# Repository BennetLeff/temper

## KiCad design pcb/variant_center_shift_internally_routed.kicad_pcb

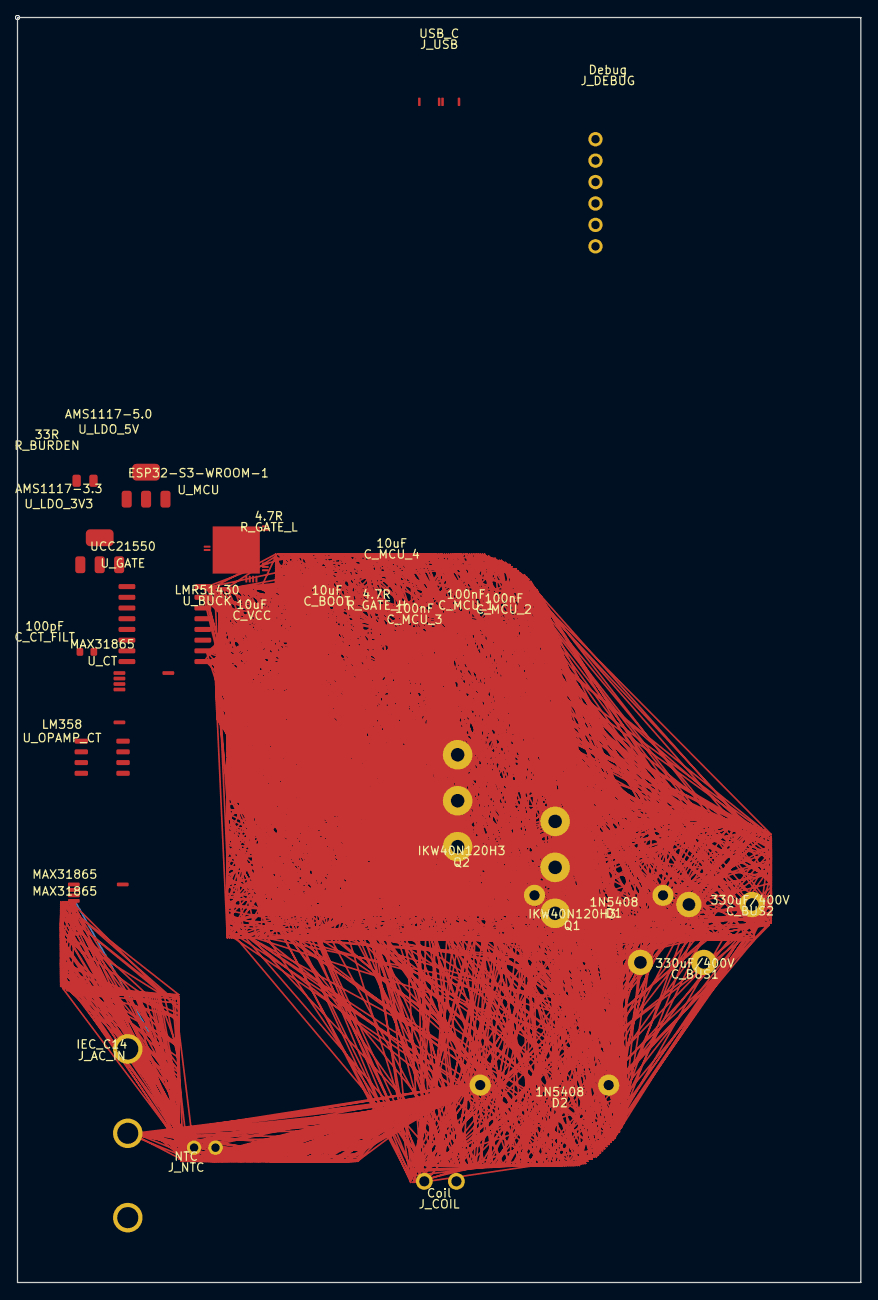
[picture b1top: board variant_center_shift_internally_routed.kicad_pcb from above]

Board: 4 copper layers, 100.0 x 150.0 mm, 33 parts (0 on the bottom side), 23 nets.

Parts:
C_BOOT: 10uF; C_0805_2012Metric
C_BUS1, C_BUS2: 330uF/400V; CP_Radial_D18.0mm_P7.50mm
C_CT_FILT: 100pF; C_0603_1608Metric
C_MCU_1, C_MCU_2, C_MCU_3: 100nF; C_0402_1005Metric
C_MCU_4: 10uF; C_0402_1005Metric
C_VCC: 10uF; C_0805_2012Metric
D1, D2: 1N5408; D_DO-201AD_P15.24mm_Horizontal
J_AC_IN: IEC_C14; IEC_C14_Male
J_COIL: Coil; PhoenixContact_MCV_1,5_2-G-3.81_1x02_P3.81mm_Vertical
J_DEBUG: Debug; PinHeader_1x06_P2.54mm_Vertical
J_NTC: NTC; PinHeader_1x02_P2.54mm_Vertical
J_USB: USB_C; USB_C_Receptacle_HRO_TYPE-C-31-M-12
MAX31865: MAX31865; TSSOP-20_4.4x6.5mm_P0.65mm
MH1, MH2, MH3, MH4: MountingHole_3.2mm_M3
Q1, Q2: IKW40N120H3; TO-247-3_Horizontal_TabDown
R_BURDEN: 33R; R_0805_2012Metric
R_GATE_H: 4.7R; R_0805_2012Metric
R_GATE_L: 4.7R; R_0805_2012Metric
U_BUCK: LMR51430; SOT-23-6
U_CT: MAX31865; TSSOP-20_4.4x6.5mm_P0.65mm
U_GATE: UCC21550; SOIC-16W_7.5x10.3mm_P1.27mm
U_LDO_3V3: AMS1117-3.3; SOT-223-3_TabPin2
U_LDO_5V: AMS1117-5.0; SOT-223-3_TabPin2
U_MCU: ESP32-S3-WROOM-1; QFN-56-1EP_7x7mm_P0.4mm_EP5.6x5.6mm
U_OPAMP_CT: LM358; SOIC-8_3.9x4.9mm_P1.27mm

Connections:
+3V3: C_MCU_1.1, C_MCU_2.1, C_MCU_3.1, C_MCU_4.1, J_DEBUG.2, MAX31865.20, U_CT.20, U_LDO_3V3.2, U_LDO_3V3.4, U_MCU.1
+5V: U_BUCK.2, U_BUCK.4, U_LDO_3V3.3, U_LDO_5V.2, U_LDO_5V.4, U_OPAMP_CT.7, U_OPAMP_CT.8
+15V: C_VCC.1, U_BUCK.3, U_GATE.1, U_GATE.11, U_LDO_5V.3
AC_L: D1.1, J_AC_IN.1
AC_N: D2.2, J_AC_IN.2
CGND: C_VCC.2, U_GATE.5, U_GATE.6, U_GATE.7, U_GATE.8
DC_BUS+: C_BUS1.1, C_BUS2.1, D1.2, Q1.3
GATE_H: Q1.1, R_GATE_H.1, R_GATE_H.2, U_GATE.15
GATE_L: Q2.1, R_GATE_L.1, R_GATE_L.2, U_GATE.10
GND: C_CT_FILT.2, C_MCU_1.2, C_MCU_2.2, C_MCU_3.2, C_MCU_4.2, J_AC_IN.3, J_COIL.2, J_DEBUG.1, J_NTC.2, J_USB.A1, J_USB.A12, MAX31865.10, R_BURDEN.2, U_BUCK.1, U_BUCK.5, U_BUCK.6, U_CT.10, U_LDO_3V3.1, U_LDO_5V.1, U_MCU.2, U_MCU.57, U_OPAMP_CT.4
I_SENSE: C_CT_FILT.1, R_BURDEN.1, U_MCU.15, U_OPAMP_CT.1, U_OPAMP_CT.2, U_OPAMP_CT.3, U_OPAMP_CT.5, U_OPAMP_CT.6
PGND: C_BUS1.2, C_BUS2.2, Q2.2, U_GATE.12, U_GATE.13
PWM_H: U_GATE.2, U_MCU.13
PWM_L: U_GATE.3, U_MCU.14
SPI_CLK: MAX31865.1, U_CT.1, U_MCU.20
SPI_CS_TEMP: U_CT.4, U_MCU.23
SPI_MISO: MAX31865.3, U_CT.3, U_MCU.22
SPI_MOSI: MAX31865.2, U_CT.2, U_MCU.21
SW_NODE: C_BOOT.2, J_COIL.1, Q1.2, Q2.3, U_GATE.9, U_GATE.16
TEMP_SENSE: J_NTC.1, MAX31865.4
USB_D+: J_USB.A6, U_MCU.40
USB_D-: J_USB.B6, U_MCU.41
VCC_BOOT: C_BOOT.1, U_GATE.14

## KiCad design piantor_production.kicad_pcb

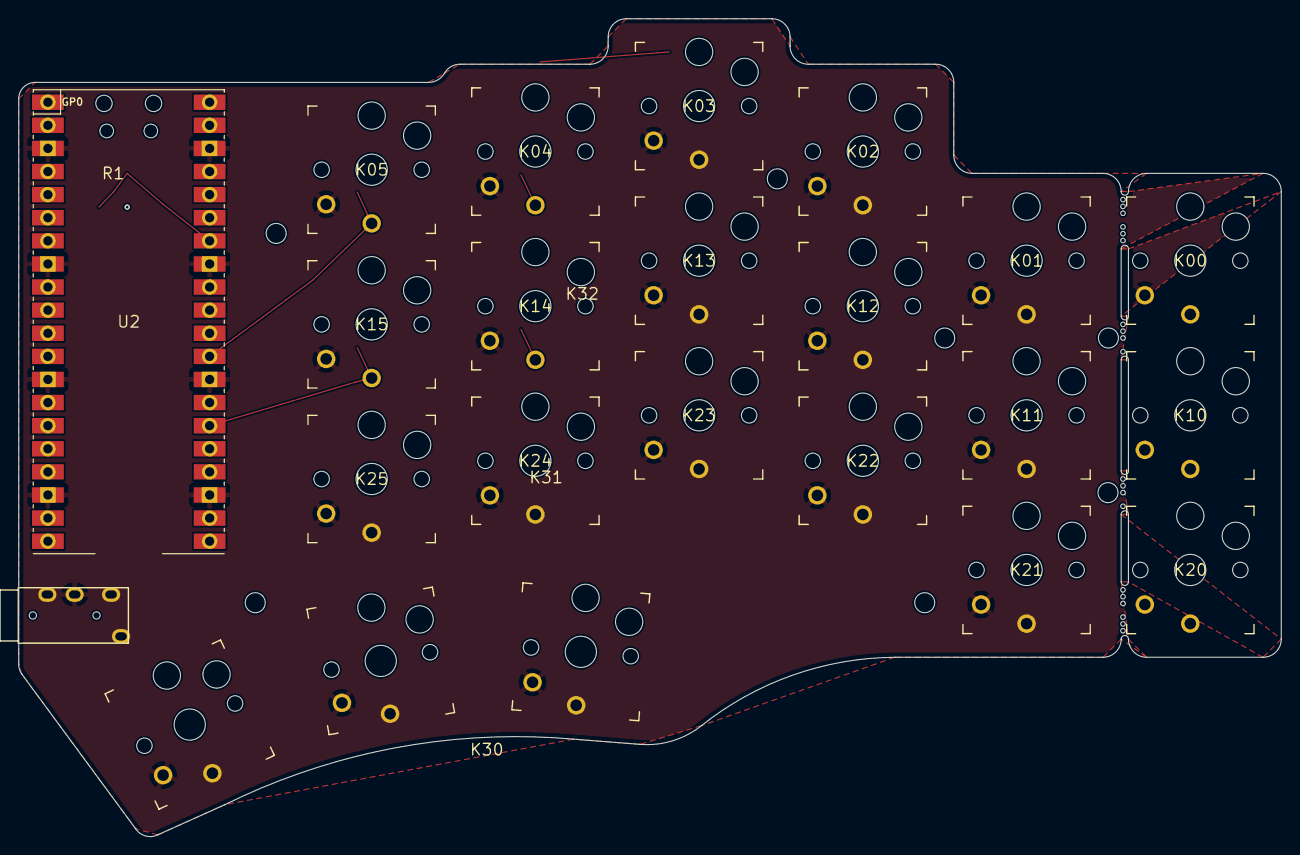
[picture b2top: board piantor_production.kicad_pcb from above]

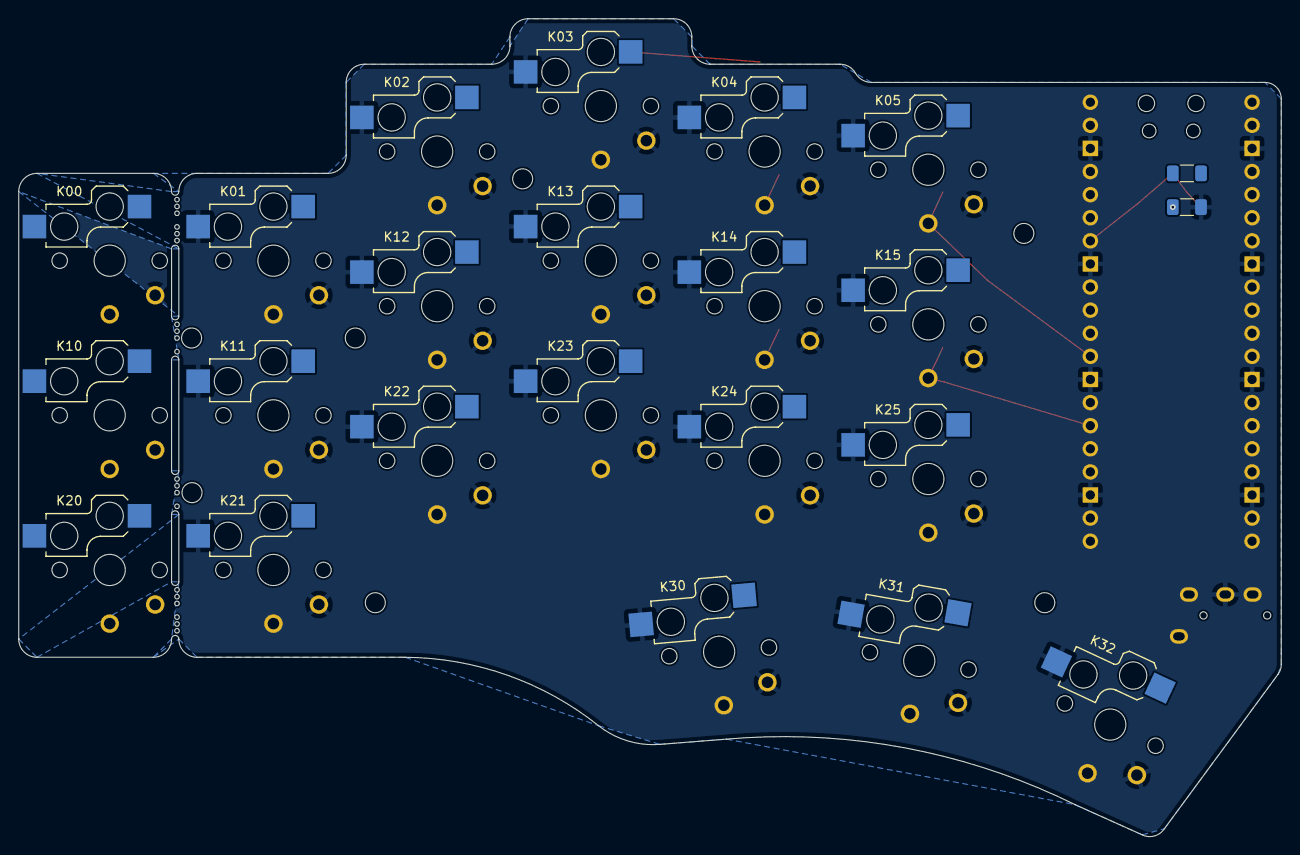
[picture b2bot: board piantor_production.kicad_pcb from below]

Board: 2 copper layers, 138.8 x 89.9 mm, 36 parts (13 on the bottom side), 27 nets.

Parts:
H1, H1#2, H2, H3, H4, H4#2, H4#3: MountingHole; MountingHole_2.2mm_M2-8mm
J1: TRRS; TRRS-PJ-320A
K00, K01, K02, K03, K04, K05, K10, K11, K12, K13, K14, K15, K20, K21, K22, K23, K24, K25, K30, K31, K32: KEYSW; Kailh_socket_PG1350_optional
MB1, MB2: MountingHole; mousebites_2
MB3, MB4: MountingHole; mousebites_3
R1: 5k6; R_1206_3216Metric_Pad1.30x1.75mm_HandSolder
R2: 10k; R_1206_3216Metric_Pad1.30x1.75mm_HandSolder
U2: Pico; RPi_Pico_SMD_TH

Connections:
/k00: K00.1, U2.15 (GPIO11)
/k01: K01.1, U2.11 (GPIO8)
/k02: K02.1, U2.7 (GPIO5)
/k03: K03.1, U2.4 (GPIO2)
/k04: K04.1, U2.27 (GPIO21)
/k05: K05.1, U2.29 (GPIO22)
/k10: K10.1, U2.16 (GPIO12)
/k11: K11.1, U2.12 (GPIO9)
/k12: K12.1, U2.9 (GPIO6)
/k13: K13.1, U2.5 (GPIO3)
/k14: K14.1, U2.25 (GPIO19)
/k15: K15.1, U2.26 (GPIO20)
/k20: K20.1, U2.17 (GPIO13)
/k21: K21.1, U2.14 (GPIO10)
/k22: K22.1, U2.10 (GPIO7)
/k23: K23.1, U2.6 (GPIO4)
/k24: K24.1, U2.22 (GPIO17)
/k25: K25.1, U2.24 (GPIO18)
/k30: K30.1, U2.21 (GPIO16)
/k31: K31.1, U2.19 (GPIO14)
/k32: K32.1, U2.20 (GPIO15)
GND: J1.3 (RING1), K00.2, K01.2, K02.2, K03.2, K04.2, K05.2, K10.2, K11.2, K12.2, K13.2, K14.2, K15.2, K20.2, K21.2, K22.2, K23.2, K24.2, K25.2, K30.2, K31.2, K32.2, R2.2, U2.3 (GND), U2.8 (GND), U2.13 (GND), U2.18 (GND), U2.23 (GND), U2.28 (GND), U2.33 (AGND), U2.38 (GND)
VBUS: R1.1, U2.40 (VBUS)
VCC: J1.2 (TIP), U2.39 (VSYS)
rx: J1.4 (RING2), U2.2 (GPIO1)
tx: J1.1 (SLEEVE), U2.1 (GPIO0)
vbus_sense: R1.2, R2.1, U2.34 (GPIO28_ADC2)
